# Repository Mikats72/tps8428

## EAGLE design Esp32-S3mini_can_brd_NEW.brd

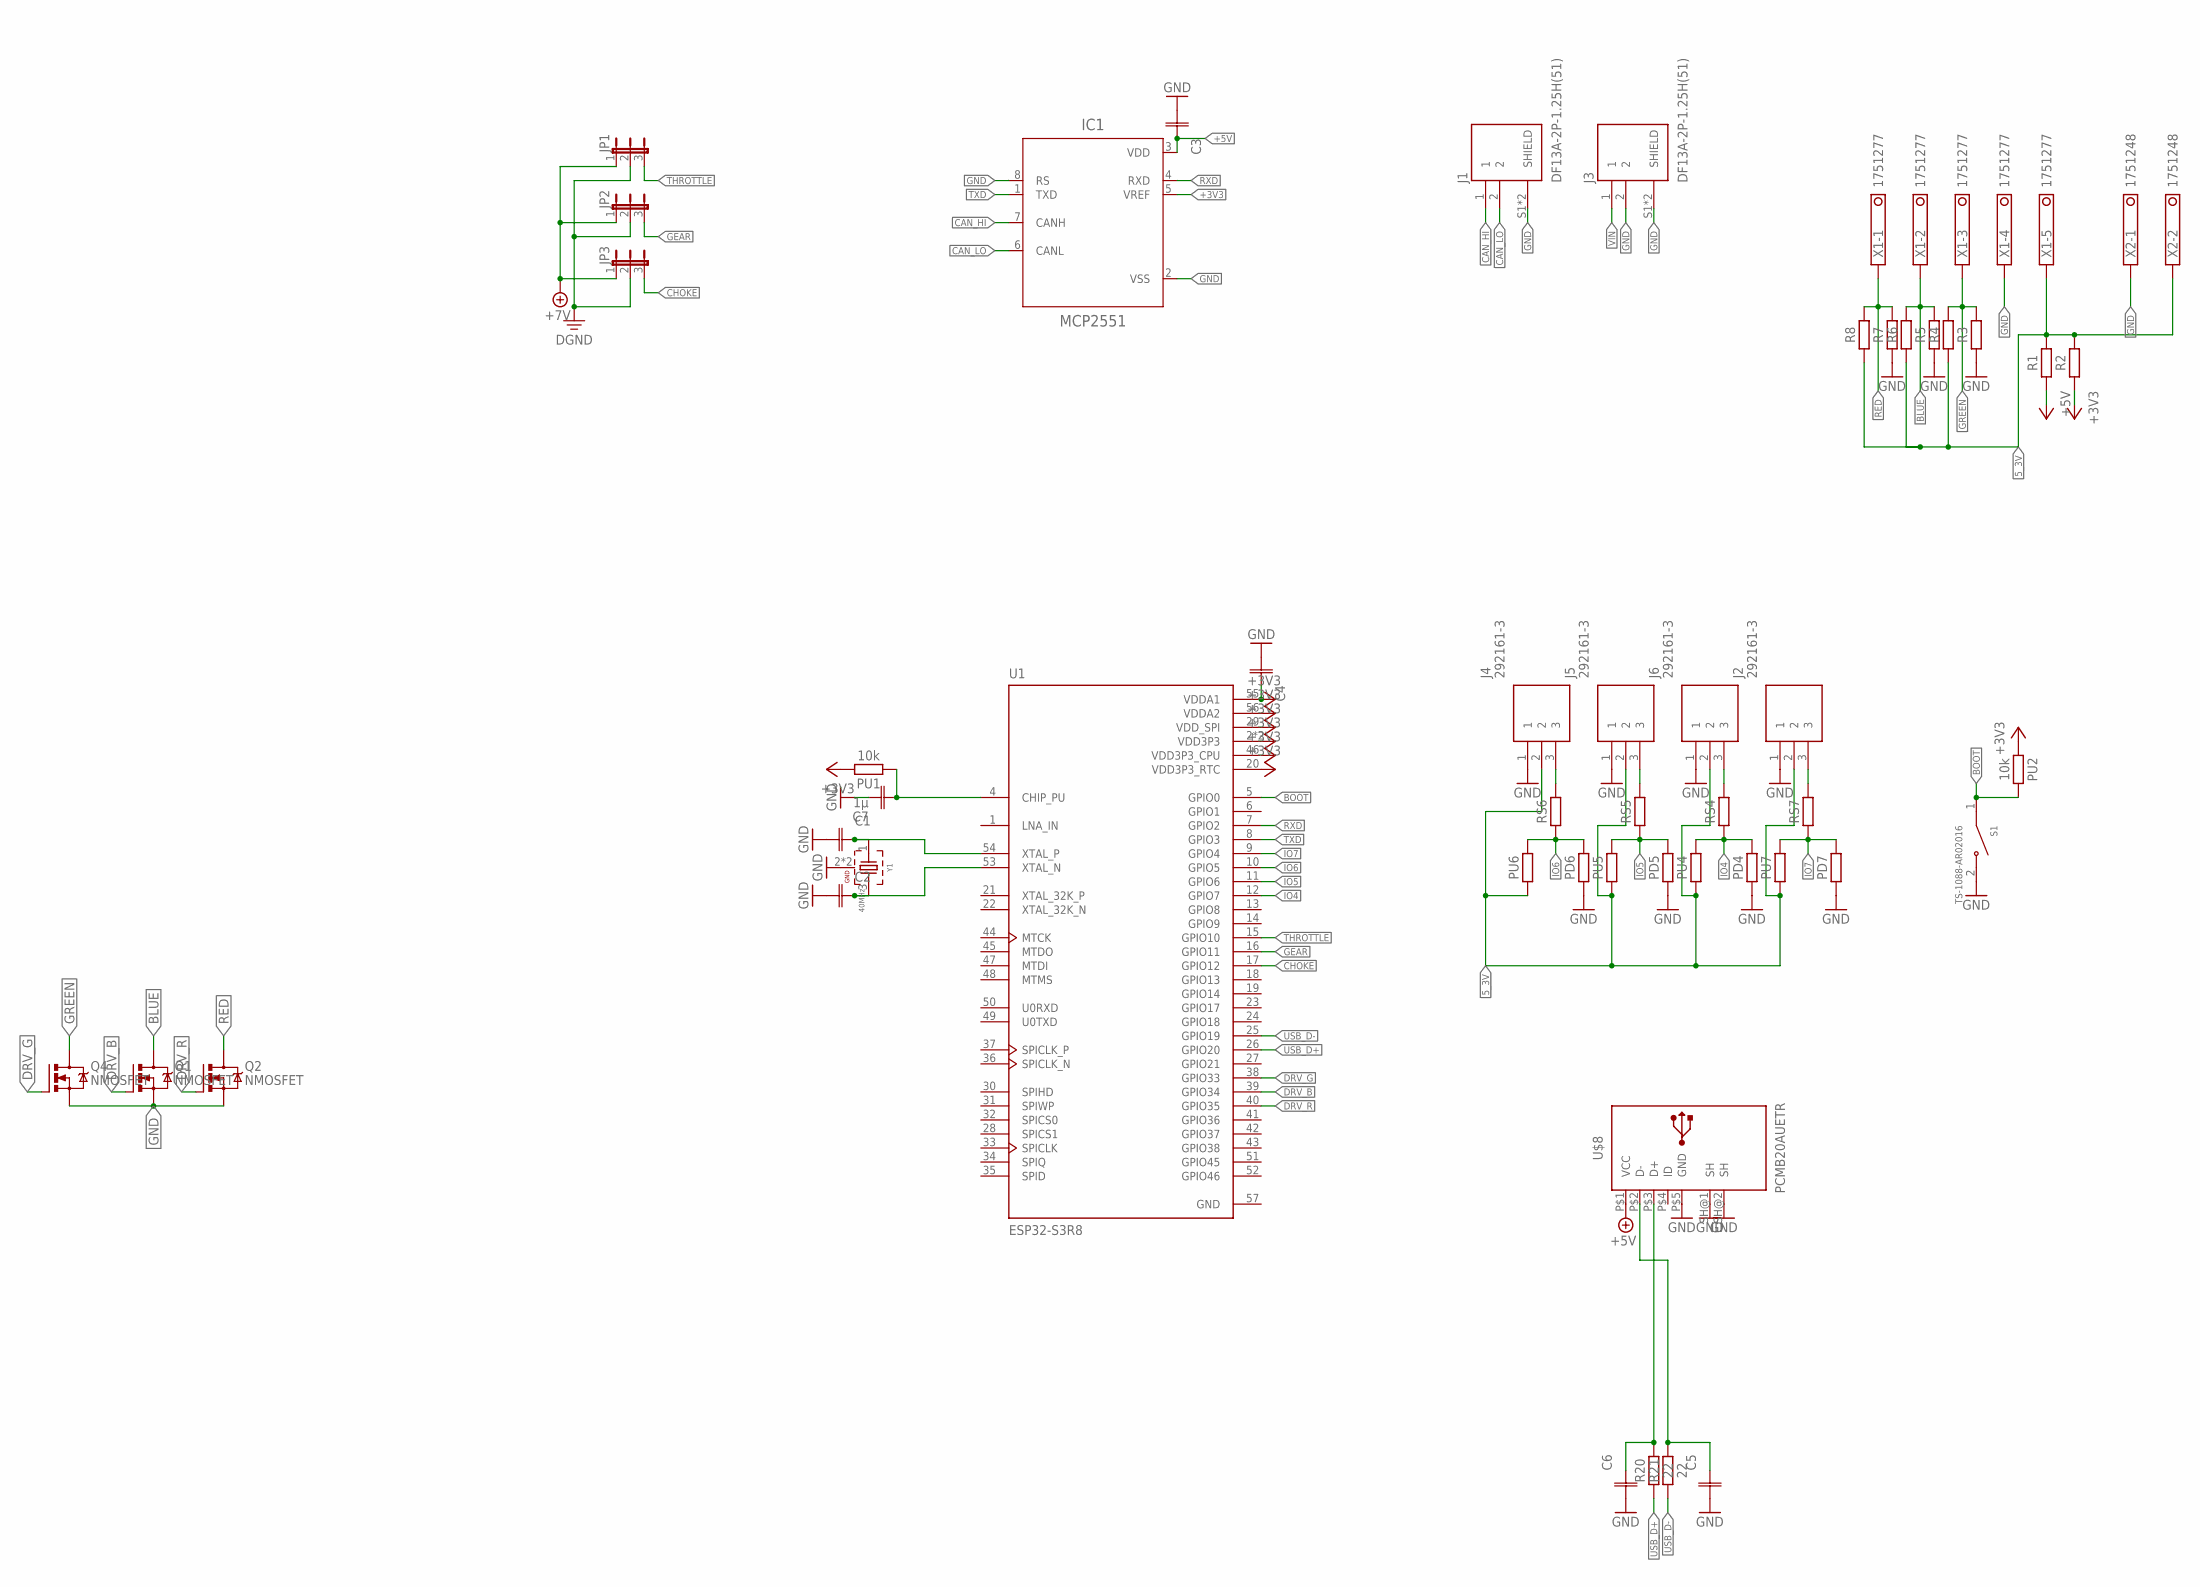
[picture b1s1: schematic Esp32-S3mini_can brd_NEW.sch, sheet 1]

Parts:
C1, C2, C3, C4: C_CHIP-0603(1608-METRIC); CAPC1608X85
C5, C6: C_CHIP-0402(1005-METRIC); CAPC1005X60
C7: 1µ; CAPC1608X85
IC1: MCP2551; SOIC127P599X175-8
J1, J3: DF13A-2P-1.25H(51); HRS_DF13A-2P-1.25H(51)
J2, J4, J5, J6: 292161-3; SHDR3W60P0X200_1X3_780X360X680
JP1, JP2, JP3: JP2E; JP2
PD4, PD5, PD6, PD7: R_CHIP-0603(1608-METRIC); RESC1608X60
PU1, PU2: 10k; RESC1608X60
PU4, PU5, PU6, PU7: R_CHIP-0603(1608-METRIC); RESC1608X60
Q1, Q2, Q4: NMOSFET; SOT23
R1, R2, R3, R4, R5, R6, R7, R8: R_CHIP-0603(1608-METRIC); RESC1608X60
R20, R21: 22; RESC1005X40
RS4, RS5, RS6, RS7: R_CHIP-0603(1608-METRIC); RESC1608X60
S1: TS-1088-AR02016; SW_TS-1088-AR02016
U1: ESP32-S3R8; QFN40P700X700X90-57N
U$8: PCMB20AUETR
X1: 1751277
X2: 1751248
Y1: 40MHz; WE-XTAL_IQXC-42

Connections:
5_3V: J2.2, J4.2, J5.2, J6.2, PU4.1, PU5.1, PU6.1, PU7.1, R1.2, R2.2, R4.1, R6.1, R8.1, X1.5, X2.2
+3V3: C4.2, IC1.5 (VREF), PU1.2, PU2.1, R2.1, U1.2 (VDD3P3), U1.3 (VDD3P3), U1.20 (VDD3P3_RTC), U1.29 (VDD_SPI), U1.46 (VDD3P3_CPU), U1.55 (VDDA1), U1.56 (VDDA2); also elsewhere on the board
+5V: C3.2, IC1.3 (VDD), R1.1, U$8.P$1 (VCC); also elsewhere on the board
+7V: JP1.1, JP2.1, JP3.1; also elsewhere on the board
BLUE: Q1.3 (D), R5.2, R6.2, X1.2
BOOT: PU2.2, S1.1, U1.5 (GPIO0)
CAN_HI: IC1.7 (CANH), J1.1
CAN_LO: IC1.6 (CANL), J1.2
CHOKE: JP3.3, U1.17 (GPIO12)
DGND: JP1.2, JP2.2, JP3.2; also elsewhere on the board
DRV_B: Q1.1 (G), U1.39 (GPIO34)
DRV_G: Q4.1 (G), U1.38 (GPIO33)
DRV_R: Q2.1 (G), U1.40 (GPIO35)
GEAR: JP2.3, U1.16 (GPIO11)
GND: C1.1, C2.1, C3.1, C4.1, C5.1, C6.1, C7.2, IC1.2 (VSS), IC1.8 (RS), J1.S1 (SHIELD), J1.S2 (SHIELD), J2.1, J3.2, J3.S1 (SHIELD), J3.S2 (SHIELD), J4.1, J5.1, J6.1, PD4.1, PD5.1, PD6.1, PD7.1, Q1.2 (S), Q2.2 (S), Q4.2 (S), R3.1, R5.1, R7.1, S1.2, U1.57 (GND), U$8.P$5 (GND), U$8.SH@1 (SH), U$8.SH@2 (SH), X1.4, X2.1, Y1.2 (GND), Y1.4 (GND); also elsewhere on the board
GREEN: Q4.3 (D), R3.2, R4.2, X1.3
IO4: PD4.2, PU4.2, RS4.1, U1.12 (GPIO7)
IO5: PD5.2, PU5.2, RS5.1, U1.11 (GPIO6)
IO6: PD6.2, PU6.2, RS6.1, U1.10 (GPIO5)
IO7: PD7.2, PU7.2, RS7.1, U1.9 (GPIO4)
unnamed: C1.2, U1.54 (XTAL_P), Y1.1
unnamed: C2.2, U1.53 (XTAL_N), Y1.3 (2)
unnamed: C7.1, PU1.1, U1.4 (CHIP_PU)
unnamed: J6.3, RS4.2
unnamed: C6.2, R20.2, U$8.P$3 (D+)
unnamed: C5.2, R21.2, U$8.P$2 (D-)
unnamed: J4.3, RS6.2
unnamed: J5.3, RS5.2
unnamed: J2.3, RS7.2
RED: Q2.3 (D), R7.2, R8.2, X1.1
RXD: IC1.4 (RXD), U1.7 (GPIO2)
THROTTLE: JP1.3, U1.15 (GPIO10)
TXD: IC1.1 (TXD), U1.8 (GPIO3)
USB_D+: R20.1, U1.26 (GPIO20)
USB_D-: R21.1, U1.25 (GPIO19)
VIN: J3.1; also elsewhere on the board

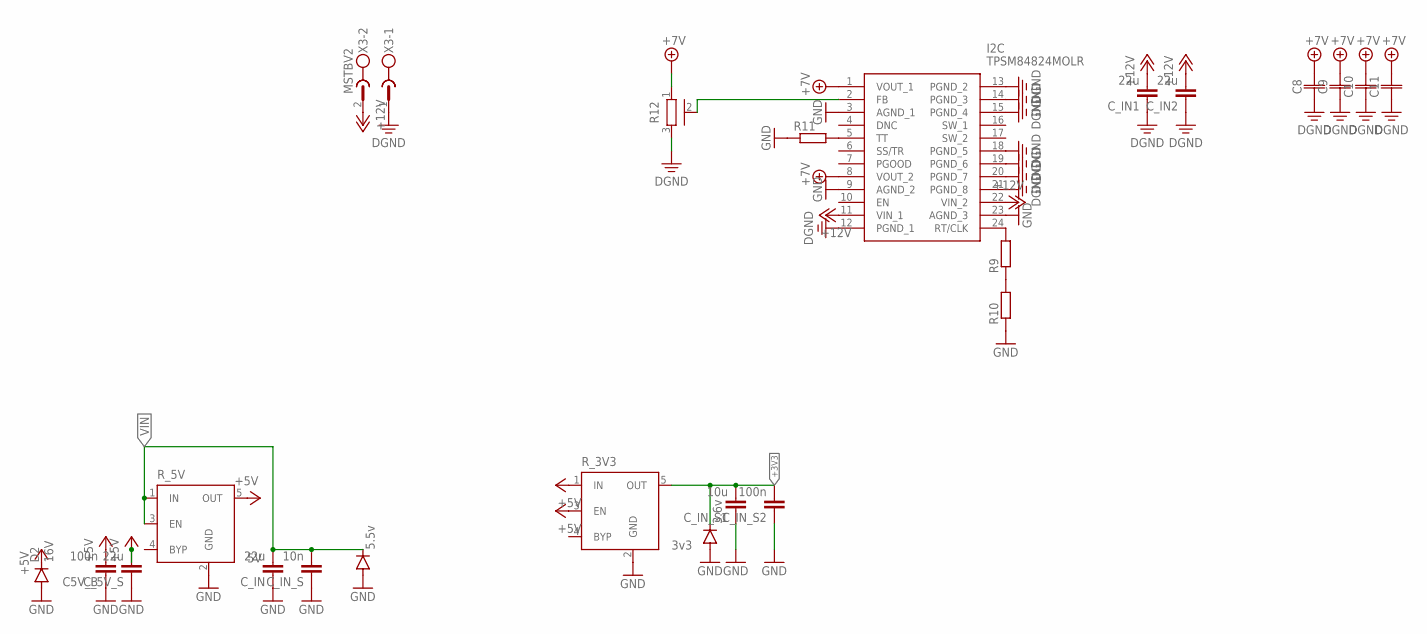
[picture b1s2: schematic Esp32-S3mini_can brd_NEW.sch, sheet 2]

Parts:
C5V_B: 100n; C0603
C8, C9, C10, C11: C_CHIP-0805(2012-METRIC); CAPC2012X110
C_5V_S: 22u; C1210K
C_IN, C_IN1, C_IN2: 22u; C1210K
C_IN_S: 10n; C0603
C_IN_S1: 10u; C0603
C_IN_S2: 100n; C0603
D1: 5.5v; SOD123
D2: 16V; SOD123
D3: 3.6v; SOD123
I2C: TPSM84824MOLR; TPSM84624MOLR
R9, R10, R11: R-EU_R0603; R0603
R12: PV36W
R_3V3: 3v3; SOT23-5
R_5V: 5V; SOT23-5
X3: MSTBV2

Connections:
+3V3: C_IN_S1.2, C_IN_S2.2, D3.C, R_3V3.5 (OUT); also elsewhere on the board
+5V: C5V_B.2, C_5V_S.2, D2.C, R_3V3.1 (IN), R_3V3.3 (EN), R_5V.5 (OUT); also elsewhere on the board
+7V: C8.2, C9.2, C10.2, C11.2, I2C.1 (VOUT_1), I2C.8 (VOUT_2), R12.1; also elsewhere on the board
+12V: C_IN1.2, C_IN2.2, I2C.11 (VIN_1), I2C.22 (VIN_2), X3.2; also elsewhere on the board
DGND: C8.1, C9.1, C10.1, C11.1, C_IN1.1, C_IN2.1, I2C.12 (PGND_1), I2C.13 (PGND_2), I2C.14 (PGND_3), I2C.15 (PGND_4), I2C.18 (PGND_5), I2C.19 (PGND_6), I2C.20 (PGND_7), I2C.21 (PGND_8), R12.3, X3.1; also elsewhere on the board
GND: C5V_B.1, C_5V_S.1, C_IN.1, C_IN_S.1, C_IN_S1.1, C_IN_S2.1, D1.A, D2.A, D3.A, I2C.3 (AGND_1), I2C.9 (AGND_2), I2C.23 (AGND_3), R10.1, R11.1, R_3V3.2 (GND), R_5V.2 (GND); also elsewhere on the board
unnamed: I2C.24 (RT/CLK), R9.2
unnamed: R9.1, R10.2
unnamed 33: I2C.2 (FB), R12.2; also elsewhere on the board
unnamed: I2C.5 (TT), R11.2
VIN: C_IN.2, C_IN_S.2, D1.C, R_5V.1 (IN), R_5V.3 (EN); also elsewhere on the board

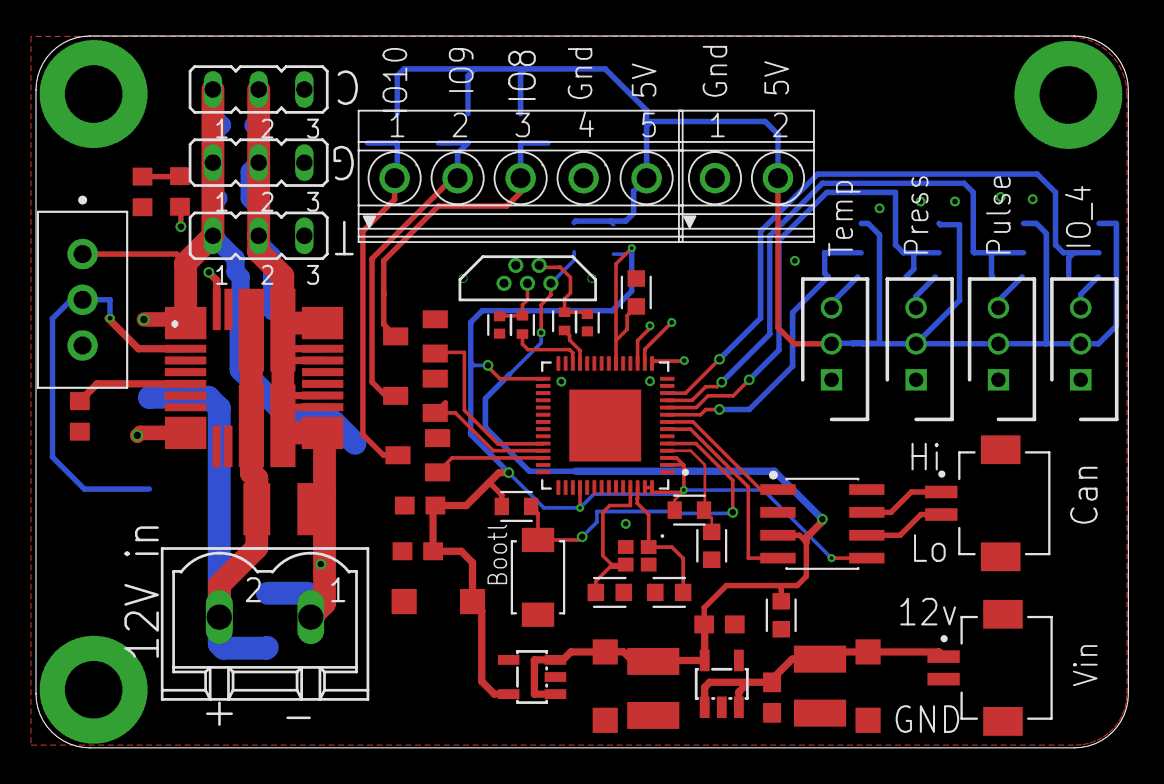
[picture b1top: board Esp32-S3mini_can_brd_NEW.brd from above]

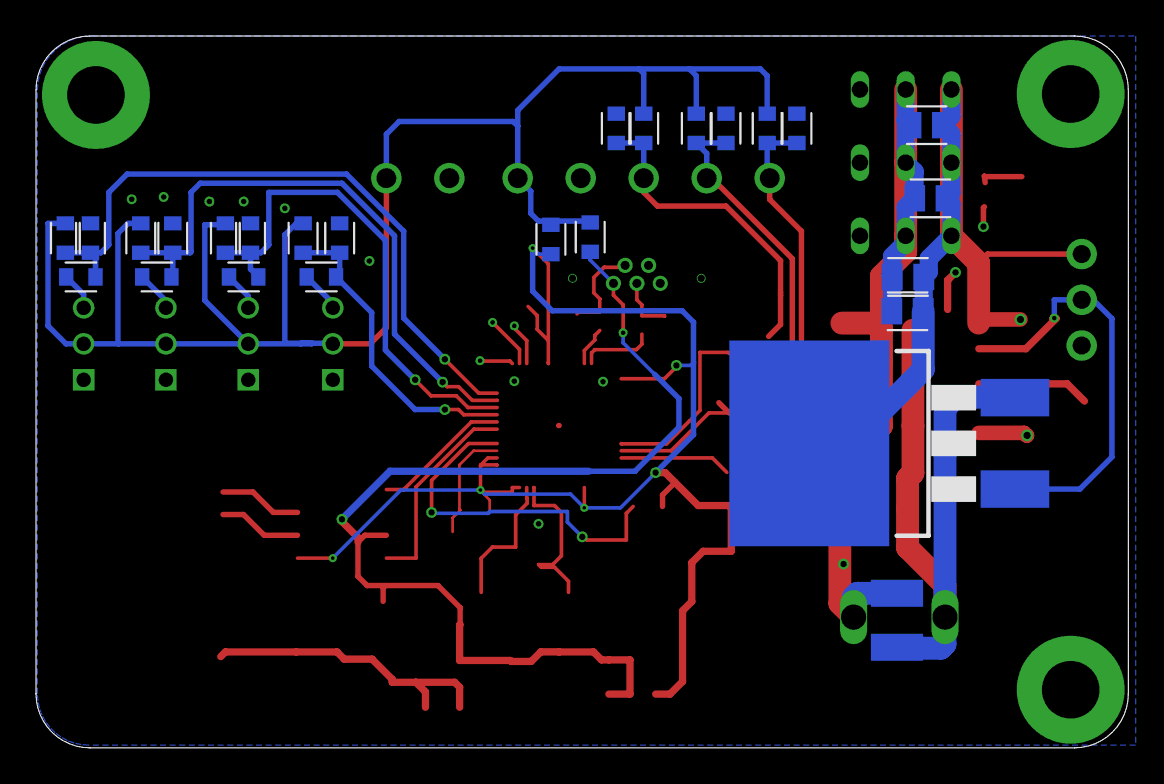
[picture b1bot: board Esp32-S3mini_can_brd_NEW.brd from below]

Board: 4 copper layers, 60.7 x 39.5 mm, 74 parts (26 on the bottom side), 41 nets.

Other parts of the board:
IC3: LM317BD2T; D2PACK

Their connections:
+7V: IC3.2; also elsewhere on the board
+12V: IC3.3; also elsewhere on the board
unnamed 33: IC3.1; also elsewhere on the board

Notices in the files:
parts and their libraries:
Wurth_Quartz Crystals: Copyright: Würth Elektronik
